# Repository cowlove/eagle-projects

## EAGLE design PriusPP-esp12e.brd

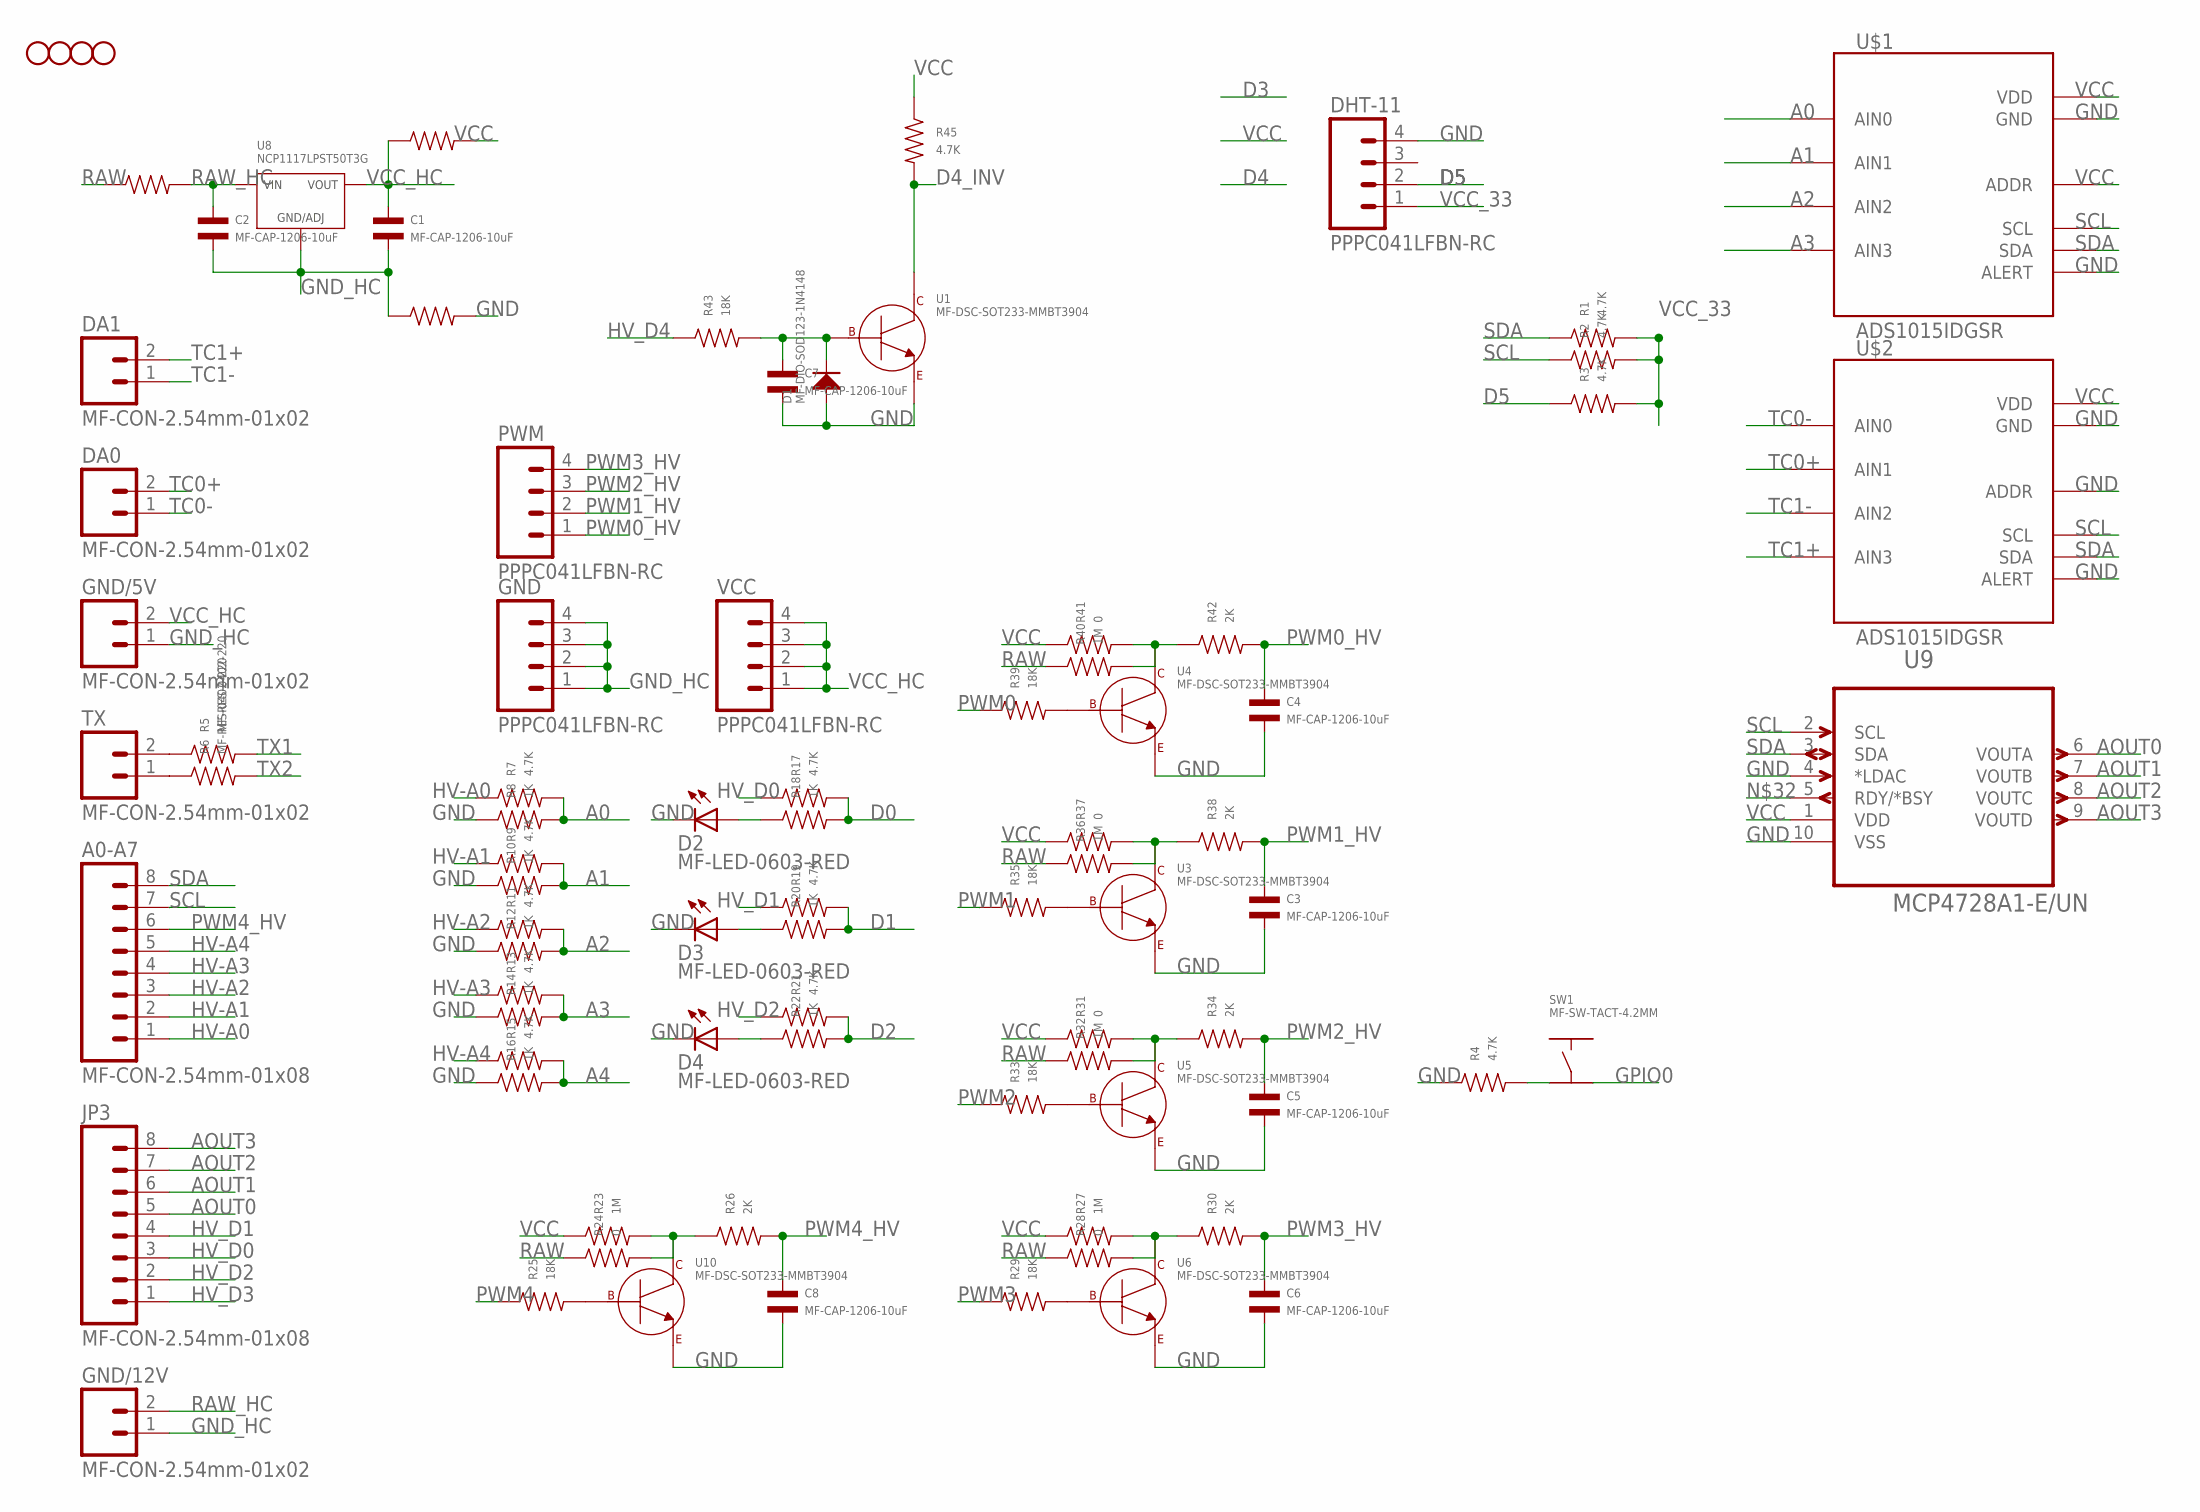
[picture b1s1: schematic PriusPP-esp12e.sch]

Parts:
A0-A7: MF-CON-2.54mm-01x08; 1X08
C1, C2, C3, C4, C5, C6, C7, C8: MF-CAP-1206-10uF; C1206
D1: MF-DIO-SOD123-1N4148; SOD-123
D2, D3, D4: MF-LED-0603-RED; LED-0603
DA0, DA1: MF-CON-2.54mm-01x02; 1X02
DHT-11: PPPC041LFBN-RC; 1X04
GND: PPPC041LFBN-RC; 1X04
GND/5V, GND/12V: MF-CON-2.54mm-01x02; 1X02
JP3: MF-CON-2.54mm-01x08; 1X08
PWM: PPPC041LFBN-RC; 1X04
R1, R2, R3, R4, R7, R9, R11, R13, R15, R17, R19, R21, R45: 4.7K; R0402
R5, R6: MF-RES-0402-220; R0402
R8, R10, R12, R14, R16, R18, R20, R22: 1K; R0402
R23, R27, R32, R36, R40: 1M; R0402
R24, R28, R31, R37, R41: 0; R0402
R25, R29, R33, R35, R39, R43: 18K; R0402
R26, R30, R34, R38, R42: 2K; R0402
RIN7, RIN8, RIN19: MF-RES-0603-0; 1206
STANDOFF2, STANDOFF3, STANDOFF4, STANDOFF5: STAND-OFF
SW1: MF-SW-TACT-4.2MM; TACT4.2MM
TX: MF-CON-2.54mm-01x02; 1X02
U1, U3, U4, U5, U6, U10: MF-DSC-SOT233-MMBT3904; SOT-23-3
U8: NCP1117LPST50T3G; SOT-223-3
U9: MCP4728A1-E/UN; SOP50P490X110-10N
U$1, U$2: ADS1015IDGSR; MSOP10_0.5
VCC: PPPC041LFBN-RC; 1X04

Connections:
A0: R7.P$2, R8.P$2, U$1.4 (AIN0)
A1: R9.P$2, R10.P$2, U$1.5 (AIN1)
A2: R11.P$2, R12.P$2, U$1.6 (AIN2)
A3: R13.P$2, R14.P$2, U$1.7 (AIN3)
A4: R15.P$2, R16.P$2
AOUT0: JP3.5, U9.6 (VOUTA)
AOUT1: JP3.6, U9.7 (VOUTB)
AOUT2: JP3.7, U9.8 (VOUTC)
AOUT3: JP3.8, U9.9 (VOUTD)
D0: R17.P$2, R18.P$2
D1: R19.P$2, R20.P$2
D2: R21.P$2, R22.P$2
D4_INV: R45.P$2, U1.P$3 (COLLECTOR)
D5: DHT-11.2, R3.P$1
GND: C3.P$2, C4.P$2, C5.P$2, C6.P$2, C7.P$2, C8.P$2, D1.ANODE, D2.C, D3.C, D4.C, DHT-11.4, R4.P$1, R8.P$1, R10.P$1, R12.P$1, R14.P$1, R16.P$1, RIN8.2, U1.P$2 (EMITTER), U3.P$2 (EMITTER), U4.P$2 (EMITTER), U5.P$2 (EMITTER), U6.P$2 (EMITTER), U9.4 (*LDAC), U9.10 (VSS), U10.P$2 (EMITTER), U$1.2 (ALERT), U$1.3 (GND), U$2.1 (ADDR), U$2.2 (ALERT), U$2.3 (GND)
GND_HC: C1.P$2, C2.P$2, GND.1, GND.2, GND.3, GND.4, GND/5V.1, GND/12V.1, RIN8.1, U8.P$2 (GND/ADJ)
GPIO0: SW1.P$4
HV-A0: A0-A7.1, R7.P$1
HV-A1: A0-A7.2, R9.P$1
HV-A2: A0-A7.3, R11.P$1
HV-A3: A0-A7.4, R13.P$1
HV-A4: A0-A7.5, R15.P$1
HV_D0: JP3.3, R17.P$1
HV_D1: JP3.4, R19.P$1
HV_D2: JP3.2, R21.P$1
HV_D3: JP3.1
HV_D4: R43.P$1
N1: D3.A, R20.P$1
N2: D4.A, R22.P$1
N155: D2.A, R18.P$1
unnamed: R5.P$1, TX.2
unnamed: R25.P$2, U10.P$1 (BASE)
unnamed: C7.P$1, D1.CATHODE, R43.P$2, U1.P$1 (BASE)
unnamed: R29.P$2, U6.P$1 (BASE)
unnamed: R36.P$2, R37.P$2, R38.P$1, U3.P$3 (COLLECTOR)
unnamed: R6.P$1, TX.1
unnamed: R33.P$2, U5.P$1 (BASE)
unnamed: R31.P$2, R32.P$2, R34.P$1, U5.P$3 (COLLECTOR)
unnamed: R35.P$2, U3.P$1 (BASE)
unnamed: R40.P$2, R41.P$2, R42.P$1, U4.P$3 (COLLECTOR)
unnamed: R39.P$2, U4.P$1 (BASE)
unnamed: R27.P$2, R28.P$2, R30.P$1, U6.P$3 (COLLECTOR)
unnamed: R23.P$2, R24.P$2, R26.P$1, U10.P$3 (COLLECTOR)
unnamed: R4.P$2, SW1.P$3
PWM0: R39.P$1
PWM0_HV: C4.P$1, PWM.1, R42.P$2
PWM1: R35.P$1
PWM1_HV: C3.P$1, PWM.2, R38.P$2
PWM2: R33.P$1
PWM2_HV: C5.P$1, PWM.3, R34.P$2
PWM3: R29.P$1
PWM3_HV: C6.P$1, PWM.4, R30.P$2
PWM4: R25.P$1
PWM4_HV: A0-A7.6, C8.P$1, R26.P$2
RAW: R24.P$1, R28.P$1, R32.P$1, R36.P$1, R40.P$1, RIN19.1
RAW_HC: C2.P$1, GND/12V.2, RIN19.2, U8.P$4 (VIN)
SCL: A0-A7.7, R2.P$1, U9.2 (SCL), U$1.10 (SCL), U$2.10 (SCL)
SDA: A0-A7.8, R1.P$1, U9.3 (SDA), U$1.9 (SDA), U$2.9 (SDA)
TC0+: DA0.2, U$2.5 (AIN1)
TC0-: DA0.1, U$2.4 (AIN0)
TC1+: DA1.2, U$2.7 (AIN3)
TC1-: DA1.1, U$2.6 (AIN2)
TX1: R5.P$2
TX2: R6.P$2
VCC: R23.P$1, R27.P$1, R31.P$1, R37.P$1, R41.P$1, R45.P$1, RIN7.2, U9.1 (VDD), U$1.1 (ADDR), U$1.8 (VDD), U$2.8 (VDD)
VCC_33: DHT-11.1, R1.P$2, R2.P$2, R3.P$2
VCC_HC: C1.P$1, GND/5V.2, RIN7.1, U8.P$1 (VOUT), U8.P$3 (VOUT), VCC.1, VCC.2, VCC.3, VCC.4

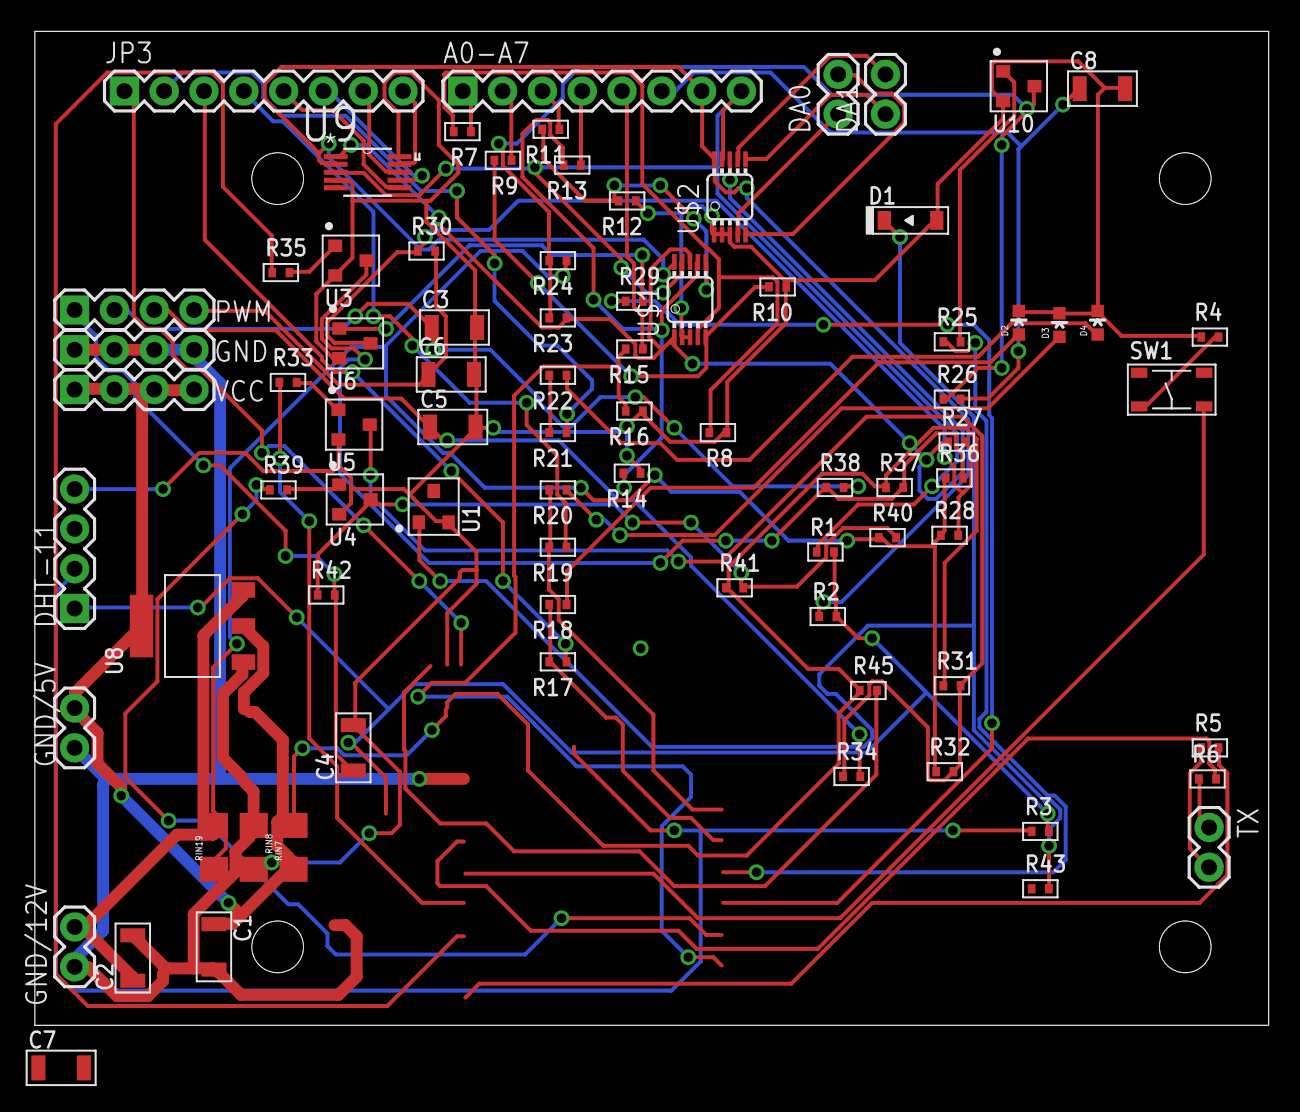
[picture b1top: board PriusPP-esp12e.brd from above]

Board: 2 copper layers, 78.7 x 63.4 mm, 85 parts (0 on the bottom side), 57 nets.

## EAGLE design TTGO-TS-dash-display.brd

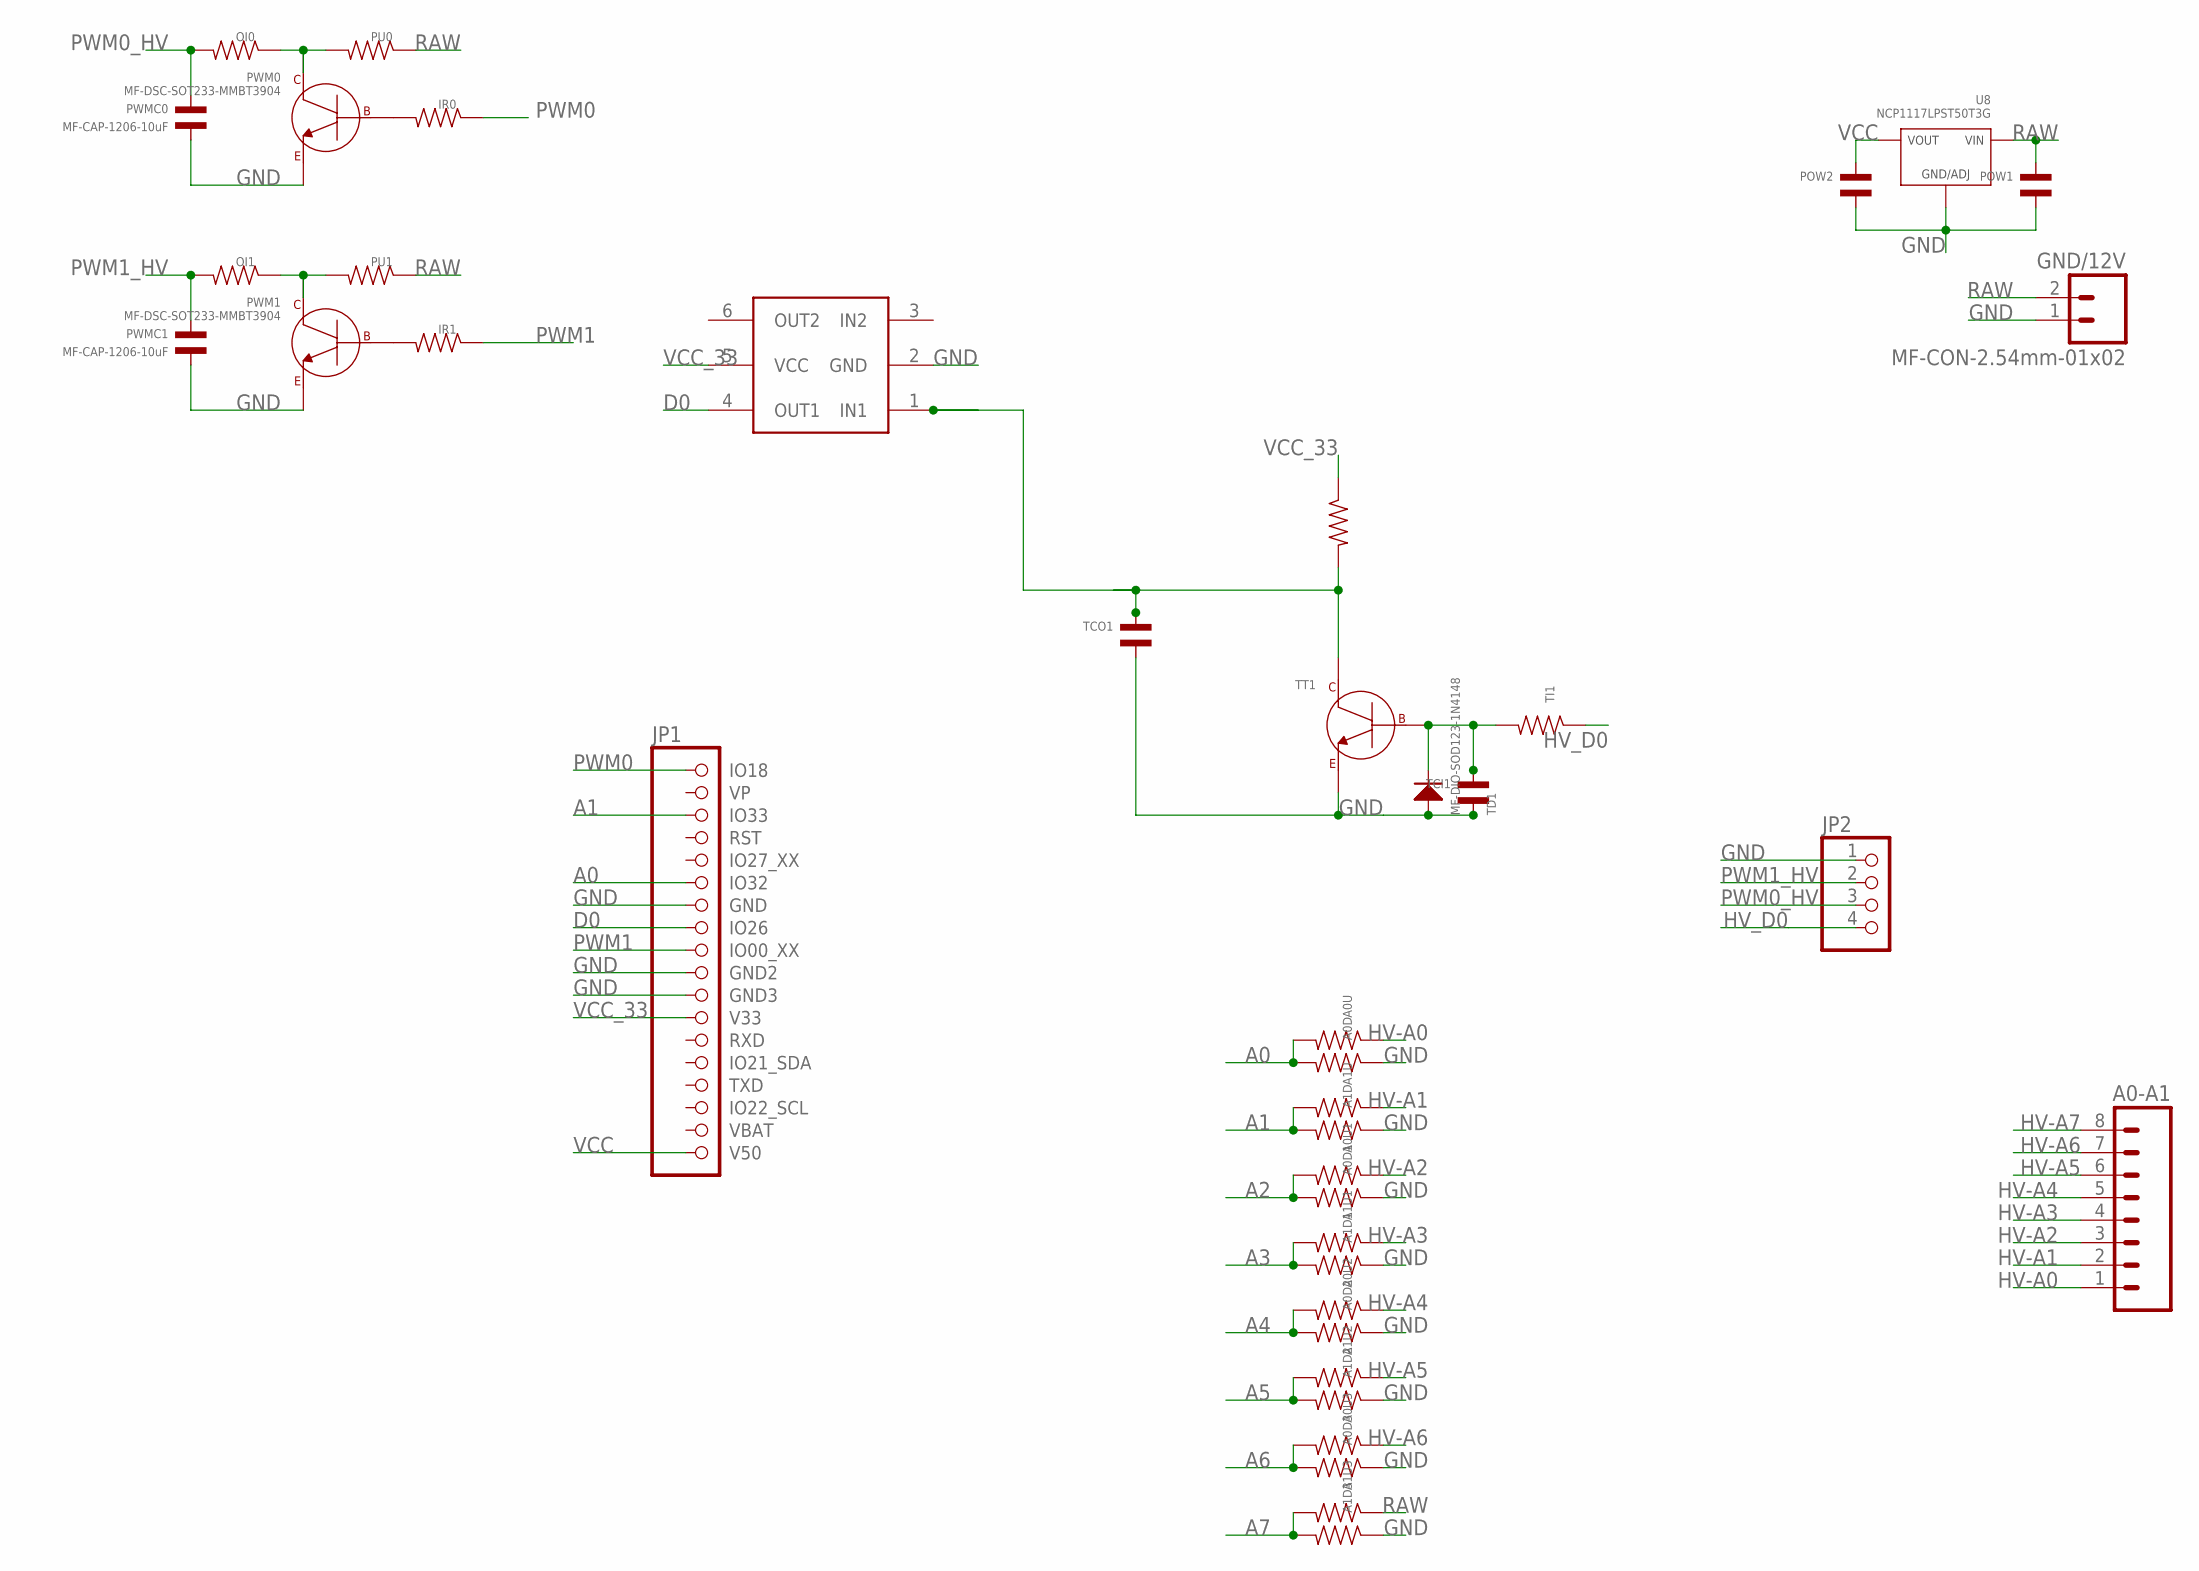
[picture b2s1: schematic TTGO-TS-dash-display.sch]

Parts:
A0-A1: MF-CON-2.54mm-01x08; 1X08
A0D, A0D1, A0D2, A0D3, A0U, A0U1, A0U2, A0U3, A1D, A1D1, A1D2, A1D3, A1U, A1U1, A1U2, A1U3: RESISTOR_1206; R1206
GND/12V: MF-CON-2.54mm-01x02; 1X02
IR0, IR1: RESISTOR_1206; R1206
JP1: 000_ESP32_D1MINI; 00_2X9
JP2: HEADER-1X4; 1X04_OVAL
OI0, OI1: RESISTOR_1206; R1206
POW1, POW2: CAPACITOR_NP_1210; C1210
PU0, PU1: RESISTOR_1206; R1206
PWM0, PWM1: MF-DSC-SOT233-MMBT3904; SOT-23-3
PWMC0, PWMC1: MF-CAP-1206-10uF; C1206
TCI1: CAPACITOR_NP_1210; C1210
TCO1: CAPACITOR_NP_1210; C1210
TD1: MF-DIO-SOD123-1N4148; SOD-123
TI1: RESISTOR_1206; R1206
TT1: MF-DSC-SOT233-MMBT3904; SOT-23-3
TU1: RESISTOR_1206; R1206
U8: NCP1117LPST50T3G; SOT-223-3
U$1: 000_DUAL-SCHMITT-INVERTER; SOT23-6

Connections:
A0: A0D.P$2, A0U.P$2, JP1.6 (IO32)
A1: A1D.P$2, A1U.P$2, JP1.3 (IO33)
A2: A0D1.P$2, A0U1.P$2
A3: A1D1.P$2, A1U1.P$2
A4: A0D2.P$2, A0U2.P$2
A5: A1D2.P$2, A1U2.P$2
A6: A0D3.P$2, A0U3.P$2
A7: A1D3.P$2, A1U3.P$2
D0: JP1.8 (IO26), U$1.4 (OUT1)
GND: A0D.P$1, A0D1.P$1, A0D2.P$1, A0D3.P$1, A1D.P$1, A1D1.P$1, A1D2.P$1, A1D3.P$1, GND/12V.1, JP1.7 (GND), JP1.10 (GND2), JP1.11 (GND3), JP2.1, POW1.P$2, POW2.P$2, PWM0.P$2 (EMITTER), PWM1.P$2 (EMITTER), PWMC0.P$2, PWMC1.P$2, TCI1.P$2, TCO1.P$2, TD1.ANODE, TT1.P$2 (EMITTER), U8.P$2 (GND/ADJ), U$1.2 (GND)
HV-A0: A0-A1.1, A0U.P$1
HV-A1: A0-A1.2, A1U.P$1
HV-A2: A0-A1.3, A0U1.P$1
HV-A3: A0-A1.4, A1U1.P$1
HV-A4: A0-A1.5, A0U2.P$1
HV-A5: A0-A1.6, A1U2.P$1
HV-A6: A0-A1.7, A0U3.P$1
HV-A7: A0-A1.8
HV_D0: JP2.4, TI1.P$1
IO21_D1: TCO1.P$1, TT1.P$3 (COLLECTOR), TU1.P$2, U$1.1 (IN1)
unnamed: TCI1.P$1, TD1.CATHODE, TI1.P$2, TT1.P$1 (BASE)
unnamed: OI1.P$1, PU1.P$2, PWM1.P$3 (COLLECTOR)
unnamed: IR1.P$2, PWM1.P$1 (BASE)
unnamed: OI0.P$1, PU0.P$2, PWM0.P$3 (COLLECTOR)
unnamed: IR0.P$2, PWM0.P$1 (BASE)
PWM0: IR0.P$1, JP1.1 (IO18)
PWM0_HV: JP2.3, OI0.P$2, PWMC0.P$1
PWM1: IR1.P$1, JP1.9 (IO00_XX)
PWM1_HV: JP2.2, OI1.P$2, PWMC1.P$1
RAW: A1U3.P$1, GND/12V.2, POW1.P$1, PU0.P$1, PU1.P$1, U8.P$4 (VIN)
VCC: JP1.18 (V50), POW2.P$1, U8.P$1 (VOUT), U8.P$3 (VOUT)
VCC_33: JP1.12 (V33), TU1.P$1, U$1.5 (VCC)

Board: 2 copper layers, 40 parts (0 on the bottom side), 31 nets, no tracks yet.

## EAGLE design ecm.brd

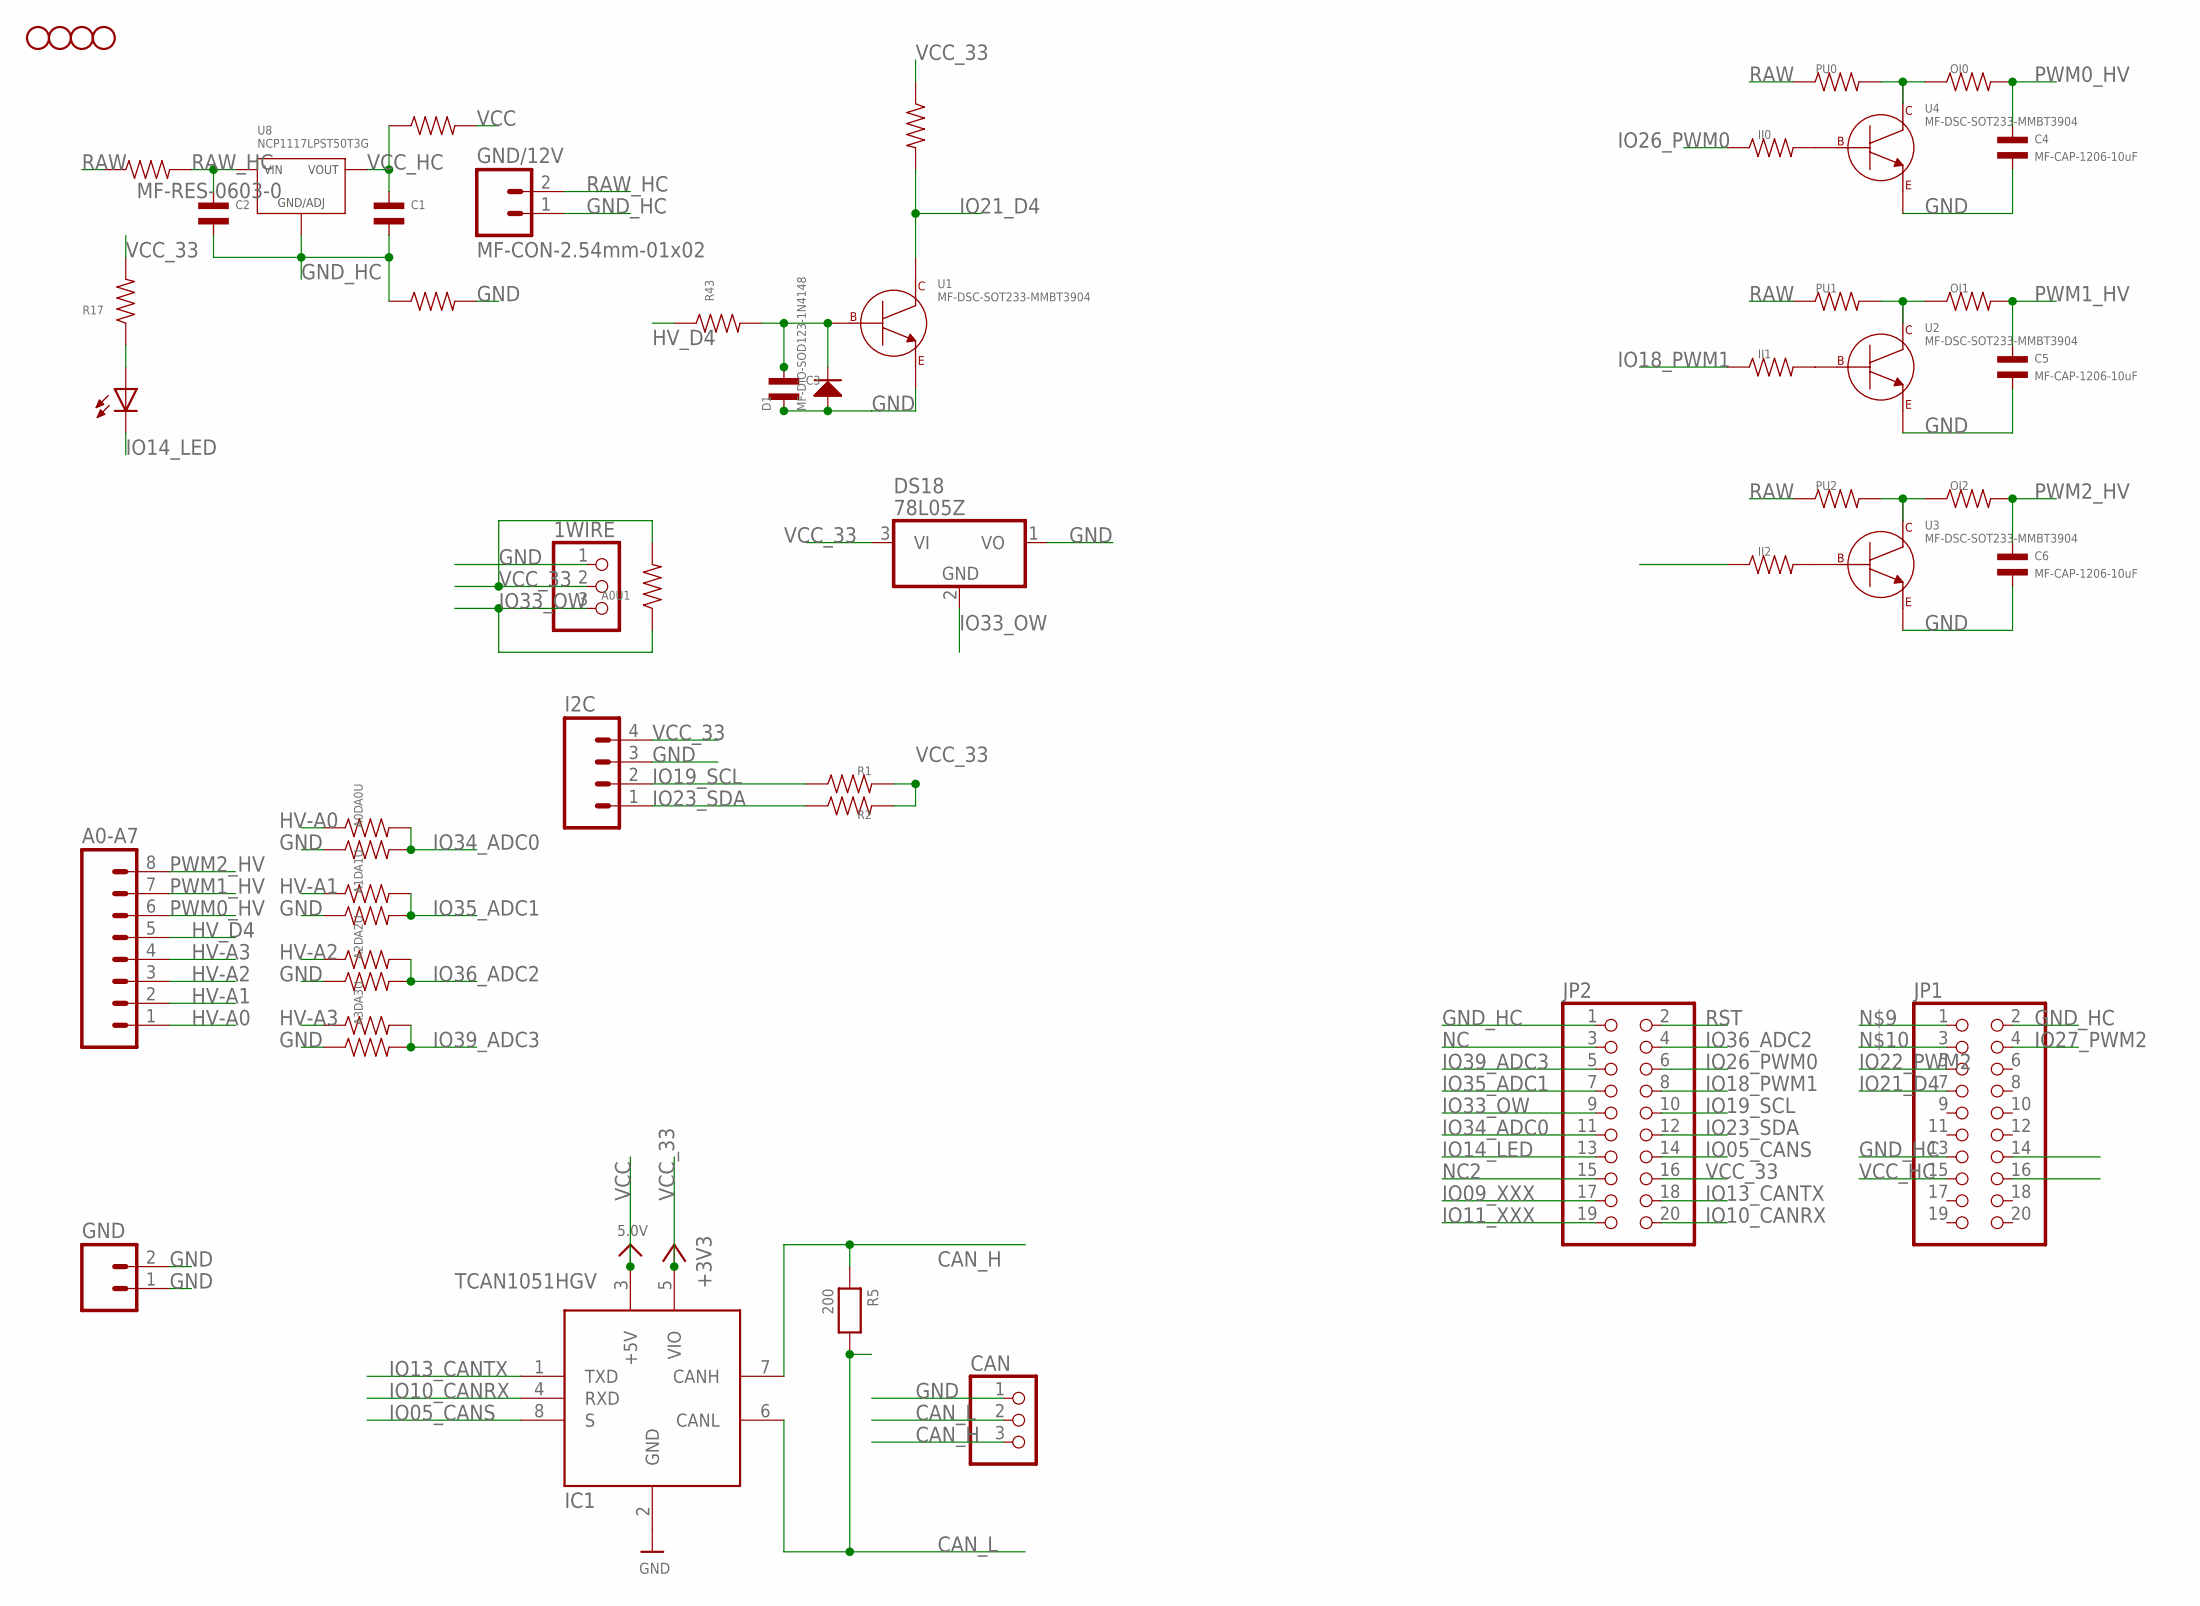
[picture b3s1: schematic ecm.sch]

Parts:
1WIRE: 1WIRE; 1X03
A0-A7: MF-CON-2.54mm-01x08; 1X08
A0D, A0U, A0U1, A1D, A1U, A2D, A2U, A3D, A3U: RESISTOR_1206; R1206
C1, C2, C3: CAPACITOR_NP_1210; C1210
C4, C5, C6: MF-CAP-1206-10uF; C1206
CAN: PINHD-1X3; 1X03
D1: MF-DIO-SOD123-1N4148; SOD-123
D2: RED; LED-1206
DS18: 78L05Z; TO92
GND: MF-CON-2.54mm-01x02; 1X02
GND/12V: MF-CON-2.54mm-01x02; 1X02
I2C: PPPC041LFBN-RC; 1X04
IC1: TCAN1051HGV; SOIC8_150MIL
II0, II1, II2: RESISTOR_1206; R1206
JP1, JP2: HEADER-2X10; 2X10
OI0, OI1, OI2: RESISTOR_1206; R1206
PU0, PU1, PU2: RESISTOR_1206; R1206
R1, R2, R17, R43, R45: RESISTOR_1206; R1206
R5: 200; 1206
RIN7, RIN8, RIN19: MF-RES-0603-0; 1206
STANDOFF2, STANDOFF3, STANDOFF4, STANDOFF5: STAND-OFF
U1, U2, U3, U4: MF-DSC-SOT233-MMBT3904; SOT-23-3
U8: NCP1117LPST50T3G; SOT-223-3

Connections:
CAN_H: CAN.3, IC1.7 (CANH), R5.1
CAN_L: CAN.2, IC1.6 (CANL), R5.2
GND: 1WIRE.1, A0D.P$1, A1D.P$1, A2D.P$1, A3D.P$1, C3.P$2, C4.P$2, C5.P$2, C6.P$2, CAN.1, D1.ANODE, DS18.1 (VO), GND.1, GND.2, I2C.3, IC1.2 (GND), RIN8.2, U1.P$2 (EMITTER), U2.P$2 (EMITTER), U3.P$2 (EMITTER), U4.P$2 (EMITTER)
GND_HC: C1.P$2, C2.P$2, GND/12V.1, JP1.2, JP1.13, JP2.1, RIN8.1, U8.P$2 (GND/ADJ)
HV-A0: A0-A7.1, A0U.P$1
HV-A1: A0-A7.2, A1U.P$1
HV-A2: A0-A7.3, A2U.P$1
HV-A3: A0-A7.4, A3U.P$1
HV_D4: A0-A7.5, R43.P$1
IO05_CANS: IC1.8 (S), JP2.14
IO09_XXX: JP2.17
IO10_CANRX: IC1.4 (RXD), JP2.20
IO11_XXX: JP2.19
IO13_CANTX: IC1.1 (TXD), JP2.18
IO14_LED: D2.C, JP2.13
IO18_PWM1: II1.P$1, JP2.8
IO19_SCL: I2C.2, JP2.10, R1.P$1
IO21_D4: JP1.7, R45.P$2, U1.P$3 (COLLECTOR)
IO22_PWM2: II2.P$1, JP1.5
IO23_SDA: I2C.1, JP2.12, R2.P$1
IO26_PWM0: II0.P$1, JP2.6
IO27_PWM2: JP1.4
IO33_OW: 1WIRE.3, A0U1.P$1, DS18.2 (GND), JP2.9
IO34_ADC0: A0D.P$2, A0U.P$2, JP2.11
IO35_ADC1: A1D.P$2, A1U.P$2, JP2.7
IO36_ADC2: A2D.P$2, A2U.P$2, JP2.4
IO39_ADC3: A3D.P$2, A3U.P$2, JP2.5
unnamed: D2.A, R17.P$1
unnamed: C3.P$1, D1.CATHODE, R43.P$2, U1.P$1 (BASE)
unnamed: OI1.P$1, PU1.P$2, U2.P$3 (COLLECTOR)
unnamed: II1.P$2, U2.P$1 (BASE)
unnamed: OI2.P$1, PU2.P$2, U3.P$3 (COLLECTOR)
unnamed: II2.P$2, U3.P$1 (BASE)
unnamed: OI0.P$1, PU0.P$2, U4.P$3 (COLLECTOR)
unnamed: II0.P$2, U4.P$1 (BASE)
NC: JP2.3
NC2: JP2.15
PWM0_HV: A0-A7.6, C4.P$1, OI0.P$2
PWM1_HV: A0-A7.7, C5.P$1, OI1.P$2
PWM2_HV: A0-A7.8, C6.P$1, OI2.P$2
RAW: PU0.P$1, PU1.P$1, PU2.P$1, RIN19.1
RAW_HC: C2.P$1, GND/12V.2, RIN19.2, U8.P$4 (VIN)
RST: JP2.2
VCC: IC1.3 (+5V), RIN7.2
VCC_33: 1WIRE.2, A0U1.P$2, DS18.3 (VI), I2C.4, IC1.5 (VIO), JP2.16, R1.P$2, R2.P$2, R17.P$2, R45.P$1
VCC_HC: C1.P$1, JP1.15, RIN7.1, U8.P$1 (VOUT), U8.P$3 (VOUT)

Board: 2 copper layers, 54 parts (0 on the bottom side), 40 nets, no tracks yet.

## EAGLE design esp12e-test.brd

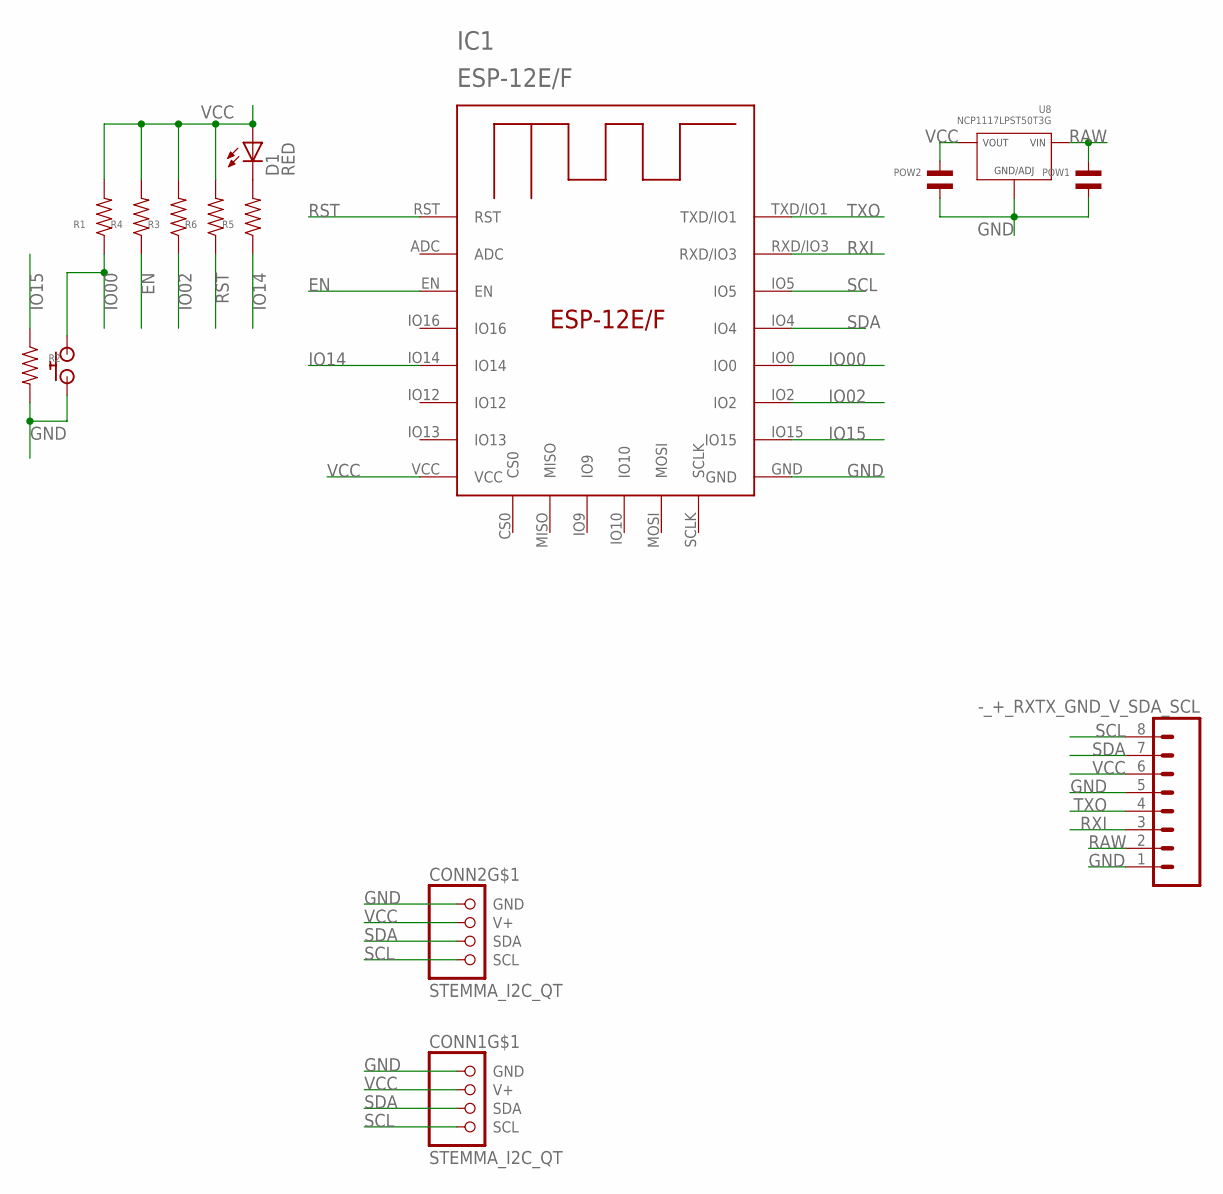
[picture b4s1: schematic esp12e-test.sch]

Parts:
-_+_RXTX_GND_V_SDA_SCL: MF-CON-2.54mm-01x08; 1X08
CONN1, CONN2: STEMMA_I2C_QT; JST_SH4
D1: RED; LED-0603
IC1: ESP-12E/F; ESP-12E
POW1, POW2: CAPACITOR_NP_1210; C1210
R1, R2, R3, R4, R5, R6: RESISTOR_0603; R0603
U8: NCP1117LPST50T3G; SOT-223-3
U$1: AMAZON_BUTTON

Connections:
EN: IC1.EN, R4.P$1
GND: -_+_RXTX_GND_V_SDA_SCL.1, -_+_RXTX_GND_V_SDA_SCL.5, CONN1.1 (GND), CONN2.1 (GND), IC1.GND, POW1.P$2, POW2.P$2, R2.P$2, U8.P$2 (GND/ADJ), U$1.2, U$1.3
IO00: IC1.IO0, R1.P$1, U$1.1, U$1.4
IO02: IC1.IO2, R3.P$1
IO14: IC1.IO14, R5.P$1
IO15: IC1.IO15, R2.P$1
unnamed: D1.C, R5.P$2
RAW: -_+_RXTX_GND_V_SDA_SCL.2, POW1.P$1, U8.P$4 (VIN)
RST: IC1.RST, R6.P$1
RXI: -_+_RXTX_GND_V_SDA_SCL.3, IC1.RXD/IO3
SCL: -_+_RXTX_GND_V_SDA_SCL.8, CONN1.4 (SCL), CONN2.4 (SCL), IC1.IO5
SDA: -_+_RXTX_GND_V_SDA_SCL.7, CONN1.3 (SDA), CONN2.3 (SDA), IC1.IO4
TXO: -_+_RXTX_GND_V_SDA_SCL.4, IC1.TXD/IO1
VCC: -_+_RXTX_GND_V_SDA_SCL.6, CONN1.2 (V+), CONN2.2 (V+), D1.A, IC1.VCC, POW2.P$1, R1.P$2, R3.P$2, R4.P$2, R6.P$2, U8.P$1 (VOUT), U8.P$3 (VOUT)

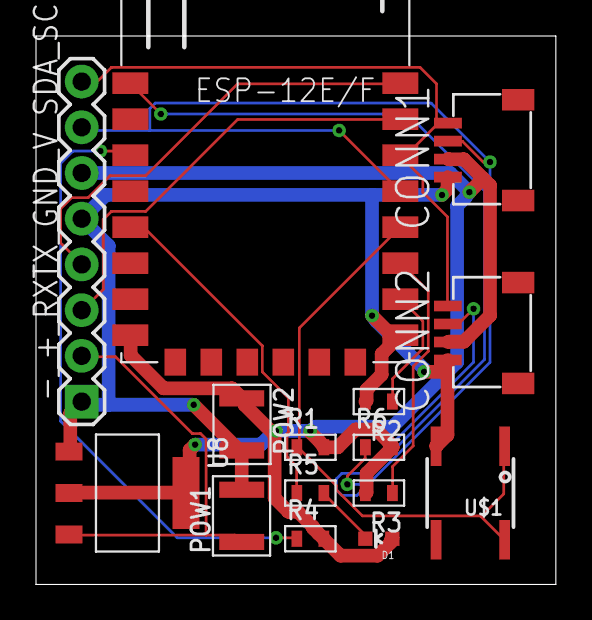
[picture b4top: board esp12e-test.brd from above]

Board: 2 copper layers, 28.9 x 30.5 mm, 15 parts (0 on the bottom side), 14 nets.

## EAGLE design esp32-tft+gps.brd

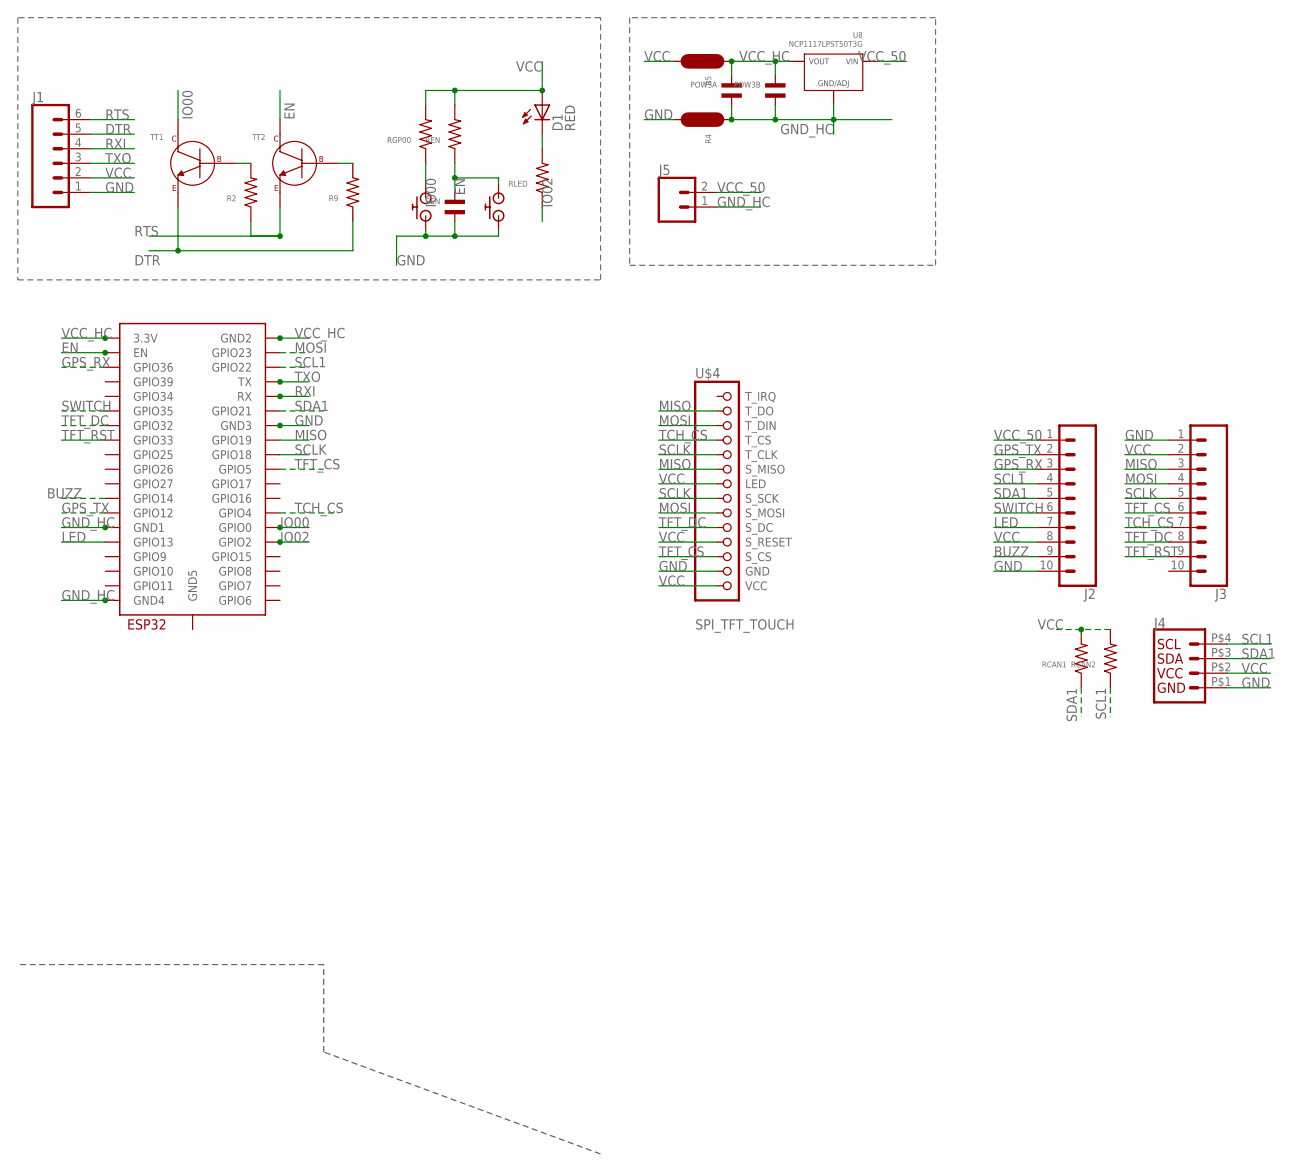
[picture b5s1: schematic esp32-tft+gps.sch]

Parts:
CEN: CAPACITOR_NP_0603; C0603
D1: RED; LED-0603
J1: CONN_06; 1X6-1.25MM-SMD
J2, J3: CONN_10; 1X10-1.25MM
J4: Vertical Qwiic Connector; JST04_1MM_HOLES
J5: CONN_02; 1X02
POW3A, POW3B: CAPACITOR_NP_0603; C0603
R2, R9: RESISTOR_0603; R0603
R4, R5: JUMPER; R0603_JMP
RCAN1, RCAN2: RESISTOR_0603; R0603
REN: RESISTOR_0603; R0603
RGP00: RESISTOR_0603; R0603
RLED: RESISTOR_0603; R0603
TT1, TT2: MF-DSC-SOT233-MMBT3904; SOT-23-3
U8: NCP1117LPST50T3G; SOT-223-3
U$1, U$2: AMAZON_BUTTONB2010; C2010
U$3: ESP32-WROOM
U$4: SPI_TFT_TOUCH; 1X14_ROUND_70

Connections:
BUZZ: J2.9, U$3.IO14 (GPIO14)
DTR: J1.5, R9.P$1, TT1.P$2 (EMITTER)
EN: CEN.P$1, REN.P$1, TT2.P$3 (COLLECTOR), U$2.P$1, U$3.EN
GND: CEN.P$2, J1.1, J2.10, J3.1, J4.P$1 (1), R4.P$2, U$1.P$2, U$2.P$2, U$3.GND3, U$4.13 (GND)
GND_HC: J5.1, POW3A.P$2, POW3B.P$2, R4.P$1, U8.P$2 (GND/ADJ), U$3.GND1, U$3.GND4
GPS_RX: J2.3, U$3.SENSOR_VP (GPIO36)
GPS_TX: J2.2, U$3.IO12 (GPIO12)
IO00: RGP00.P$1, TT1.P$3 (COLLECTOR), U$1.P$1, U$3.IO0 (GPIO0)
IO02: RLED.P$1, U$3.IO2 (GPIO2)
LED: J2.7, U$3.IO13 (GPIO13)
MISO: J3.3, U$3.IO19 (GPIO19), U$4.2 (T_DO), U$4.6 (S_MISO)
MOSI: J3.4, U$3.IO23 (GPIO23), U$4.3 (T_DIN), U$4.9 (S_MOSI)
unnamed: D1.C, RLED.P$2
unnamed: R2.P$2, TT1.P$1 (BASE)
unnamed: R9.P$2, TT2.P$1 (BASE)
RTS: J1.6, R2.P$1, TT2.P$2 (EMITTER)
RXI: J1.4, U$3.RX
SCL1: J2.4, J4.P$4 (4), RCAN2.P$1, U$3.IO22 (GPIO22)
SCLK: J3.5, U$3.IO18 (GPIO18), U$4.5 (T_CLK), U$4.8 (S_SCK)
SDA1: J2.5, J4.P$3 (3), RCAN1.P$1, U$3.IO21 (GPIO21)
SWITCH: J2.6, U$3.IO35 (GPIO35)
TCH_CS: J3.7, U$3.IO4 (GPIO4), U$4.4 (T_CS)
TFT_CS: J3.6, U$3.IO5 (GPIO5), U$4.12 (S_CS)
TFT_DC: J3.8, U$3.IO32 (GPIO32), U$4.10 (S_DC)
TFT_RST: J3.9, U$3.IO33 (GPIO33)
TXO: J1.3, U$3.TX
VCC: D1.A, J1.2, J2.8, J3.2, J4.P$2 (2), R5.P$2, RCAN1.P$2, RCAN2.P$2, REN.P$2, RGP00.P$2, U$4.7 (LED), U$4.11 (S_RESET), U$4.14 (VCC)
VCC_50: J2.1, J5.2, U8.P$4 (VIN)
VCC_HC: POW3A.P$1, POW3B.P$1, R5.P$1, U8.P$1 (VOUT), U8.P$3 (VOUT), U$3.3V3 (3.3V), U$3.GND2

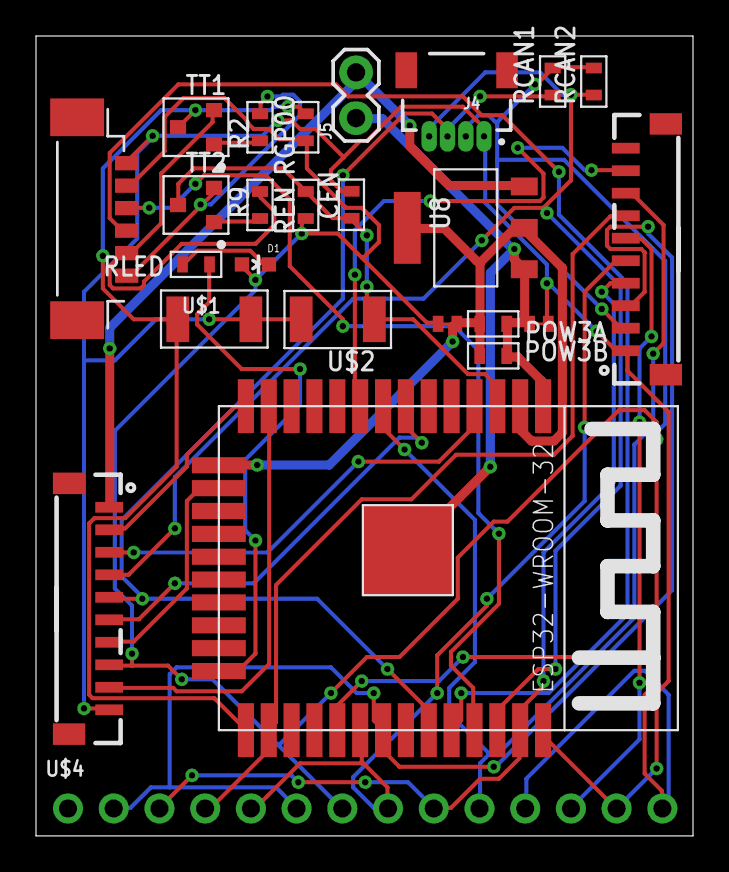
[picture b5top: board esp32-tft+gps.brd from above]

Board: 2 copper layers, 36.5 x 44.4 mm, 25 parts (0 on the bottom side), 29 nets.

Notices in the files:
parts and their libraries:
SparkFun-Electromechanical: Licensing: CC v3.0 Share-Alike You are welcome to use this library for commercial purposes.
SparkFun-DiscreteSemi: Licensing: Creative Commons ShareAlike 4.0 International - https://creativecommons.org/licenses/by-sa/4.0
